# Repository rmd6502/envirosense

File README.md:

# envirosense
Crowdsourced Environmental Sensing

The pm (particulate measure) depends on Paul Van Haastrecht's
SPS30 library at https://github.com/paulvha/sps30. Sensirion's
library doesn't work, though I imagine they'll fix that.

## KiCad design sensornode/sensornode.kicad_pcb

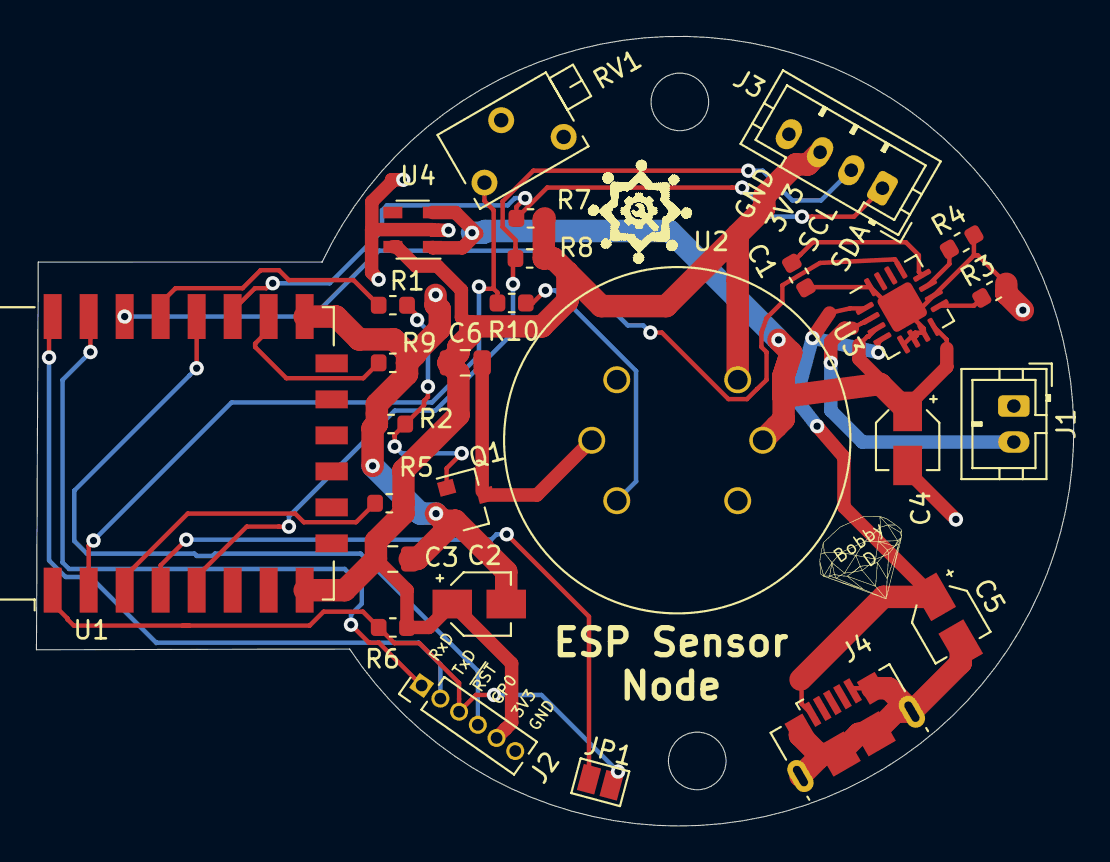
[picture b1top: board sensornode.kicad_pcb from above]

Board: 2 copper layers, 57.6 x 43.9 mm, 27 parts (0 on the bottom side), 23 nets.

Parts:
C1: 0.1u; C_0603_1608Metric
C2, C4: 10u; CP_Elec_3x5.3
C3: .1u; C_0805_2012Metric
C5: 1u; CP_Elec_3x5.3
C6: 10u ceramic; C_0805_2012Metric
J1: Conn_01x02; JST_PH_B2B-PH-K_1x02_P2.00mm_Vertical
J2: Conn_01x06_Male; PinHeader_1x06_P1.27mm_Vertical
J3: Conn_01x04_Male; JST_PH_B4B-PH-K_1x04_P2.00mm_Vertical
J4: USB_B_Micro; USB_Micro-B_GCT_USB3076-30-A
JP1: SolderJumper_2_Open; SolderJumper-2_P1.3mm_Open_Pad1.0x1.5mm
Q1: MMBT3904; SOT-23
R1: 1k; R_0603_1608Metric
R2, R5, R6, R9: 10k; R_0603_1608Metric
R3, R4: 97.6k; R_0603_1608Metric
R7, R8: 4.7k; R_0603_1608Metric
R10: 6k8; R_0603_1608Metric
RV1: 100k; Potentiometer_Bourns_3266X_Horizontal
U1: ESP-12F; ESP-12E
U2: MQ-135; MQ_13X
U3: LTC4055; QFN-16-1EP_4x4mm_P0.65mm_EP2.15x2.15mm
U4: MIC5504-3.3YM5; SOT-23-5

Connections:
+3V3: C2.1, C3.2, C6.1, J2.5, J3.3, R5.1, R6.1, R7.1, R8.1, U1.8, U2.1, U4.5
+5V: C4.1, U2.2, U3.3, U3.8, U4.1, U4.3
/GP0: J2.4, U1.18
/RX: J2.1, U1.21
/SCL: J3.2, R8.2, U1.5
/SDA: J3.1, R7.2, U1.17
/TX: J2.2, U1.22
/htron: R1.1, U1.19
/mq135_adc: R10.1, RV1.1, U1.2
/~RST: J2.3, JP1.2, R6.2, U1.1
/~acpr: U1.20, U3.13
GND: C1.2, C2.2, C3.1, C4.2, C5.2, J1.1, J2.6, J3.4, J4.5, J4.6, Q1.2, R2.1, R3.2, R4.2, R9.2, RV1.2, RV1.3, U1.15, U3.5, U3.6, U3.7, U3.10, U3.16, U3.17, U4.2
unnamed: C1.1, U3.12
unnamed: C6.2, Q1.3, U2.6
unnamed: J1.2, U3.2
unnamed: JP1.1, U1.4
unnamed: Q1.1, R1.2, R2.2
unnamed: R3.1, U3.9
unnamed: R4.1, U3.11
unnamed: R5.2, U1.3
unnamed: R9.1, U1.16
unnamed: R10.2, U2.5
VBUS: C5.1, J4.1, U3.1, U3.4

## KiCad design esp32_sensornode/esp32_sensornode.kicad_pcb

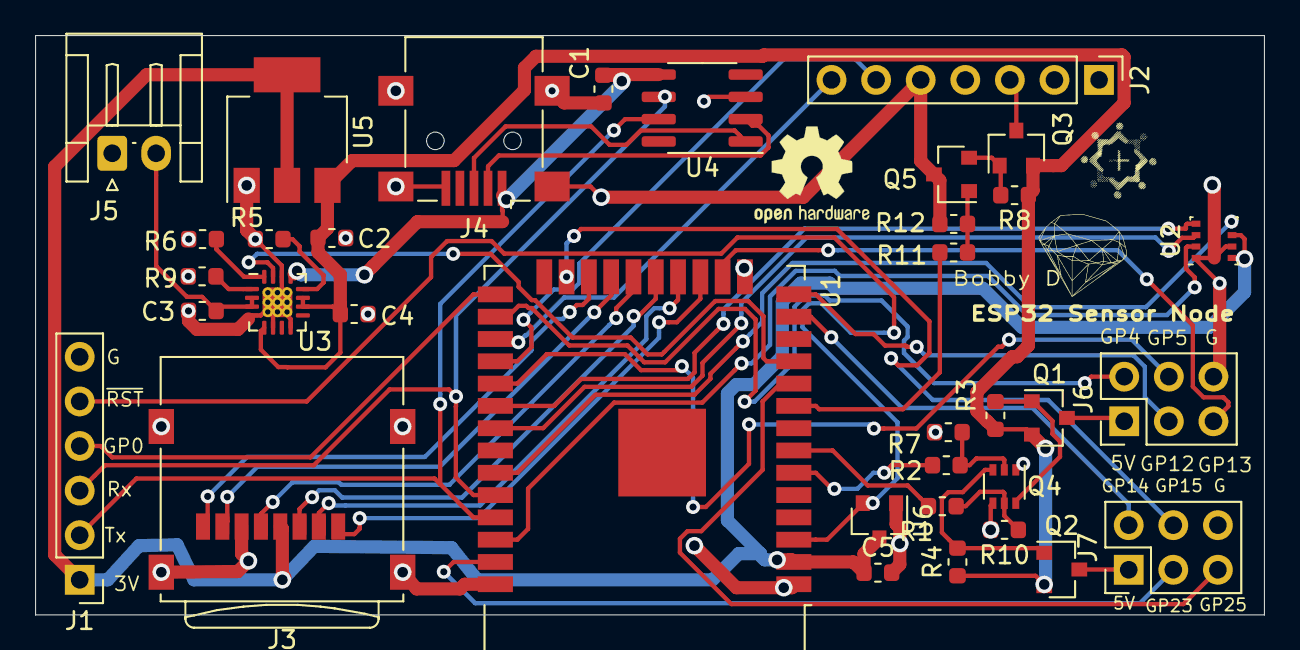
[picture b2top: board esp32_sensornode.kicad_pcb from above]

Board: 2 copper layers, 70.0 x 33.0 mm, 35 parts (0 on the bottom side), 47 nets.

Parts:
C1, C4: 2.2u 10v; C_0603_1608Metric
C2: 10u 10v; C_0603_1608Metric
C3: 2.2u 5v; C_0603_1608Metric
C5: 10u 5v; C_0603_1608Metric
J1: Conn_01x06_Female; PinHeader_1x06_P2.54mm_Vertical
J2: Conn_01x07_Male; PinHeader_1x07_P2.54mm_Vertical
J3: Micro_SD_Card; microSD_HC_Wuerth_693072010801
J4: USB_B_Mini; USB_Mini-B_Lumberg_2486_01_Horizontal
J5: Conn_01x02_Male; JST_EH_S2B-EH_1x02_P2.50mm_Horizontal
J6, J7: Conn_02x03_Odd_Even; PinHeader_2x03_P2.54mm_Vertical
Q1, Q2, Q3: NDS3332P; SOT-23
Q4: MMDT2222A; SOT-363_SC-70-6
Q5: MMBT2222A; SOT-23
R1, R2, R11: 220R; R_0603_1608Metric
R3, R4, R7, R8, R9, R10, R12: 10k; R_0603_1608Metric
R5: 1.18k; R_0603_1608Metric
R6: 1.13k; R_0603_1608Metric
U1: ESP32-WROOM-32
U2: BME280; Bosch_LGA-8_2.5x2.5mm_P0.65mm_ClockwisePinNumbering
U3: BQ24075; QFN-16-1EP_3x3mm_P0.5mm_EP1.7x1.7mm_ThermalVias
U4: CH330N; SOIC-8_3.9x4.9mm_P1.27mm
U5: LM1117-3.3; SOT-223-3_TabPin2
U6: TPS3839DBZ; SOT-23

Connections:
+3V3: C5.1, J1.1, J3.4, U1.2, U2.6, U2.8, U5.2, U6.3
+5V: C2.1, C4.1, Q1.2, Q2.2, Q3.2, R3.1, R4.1, R8.1, U3.5, U3.10, U3.11, U5.3
/BME280_MISO: U1.33, U2.5
/BME280_MOSI: U1.31, U2.3
/BME280_SCK: U1.30, U2.4
/CLK: J3.5, U1.20
/CMD: J3.3, U1.19
/D0: J3.7, U1.21
/D1: J3.8, U1.22
/D2: J3.1, U1.17
/D3: J3.2, U1.18
/EN: J1.5, U1.3, U6.2
/Enable_5V: U1.11, U3.15
/IO0: J1.4, U1.25
/IO4: J6.2, U1.26
/IO5: J6.4, U1.29
/IO12: J6.3, U1.14
/IO13: J6.5, U1.16
/IO14: J7.2, U1.13
/IO15: J7.4, U1.23
/IO23: J7.3, U1.37
/IO25: J7.5, U1.10
/RxD: J1.3, U1.34, U4.6
/SDS011_RxD: J2.6, U1.28
/SDS011_TxD: J2.7, U1.27
/TxD: J1.2, U1.35, U4.7
/USB_5V: C1.2, J4.1, U3.13, U4.5
/power_sao0: R2.2, U1.6
/power_sao1: R1.2, U1.7
/power_sds011: R11.2, U1.9
/~BME280_SS: U1.36, U2.2
GND: C1.1, C2.2, C3.2, C4.2, C5.2, J1.6, J2.5, J3.6, J3.9, J4.5, J4.6, J5.1, J6.6, J7.6, Q4.1, Q4.4, Q5.3, R5.2, R6.2, R7.2, R9.2, R10.2, R12.2, U1.1, U1.15, U1.38, U2.1, U2.7, U3.4, U3.6, U3.8, U3.14, U3.17, U4.3, U5.1, U6.1
unnamed: C3.1, J5.2, U3.2, U3.3
unnamed: J2.3, Q3.3
unnamed: J4.2, U4.2
unnamed: J4.3, U4.1
unnamed: J6.1, Q1.3
unnamed: J7.1, Q2.3
unnamed: Q1.1, Q4.6, R3.2
unnamed: Q2.1, Q4.3, R4.2
unnamed: Q3.1, Q5.2, R8.2
unnamed: Q4.2, R2.1, R7.1
unnamed: Q4.5, R1.1, R10.1
unnamed: Q5.1, R11.1, R12.1
unnamed: R5.1, U3.12
unnamed: R6.1, U3.16
unnamed: R9.1, U3.1

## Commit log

2019-05-06 add sensornode
2019-05-16 update to latest
2019-05-22 update board
2019-05-22 add c6, relayout
2019-05-22 make vbus .75mm
2019-05-23 update layout
2019-05-23 update schematic
2019-05-23 fix text items for clarity
2019-05-28 tweaks, add jumper for programming
2019-05-28 add diamond logo
2019-05-28 add missing libs and footprints, add jumper for programming
2019-05-28 add gerbers
2019-05-28 add back mounting holes?
2019-05-28 fix holes, export png and step
2019-05-29 try to get a 3d render that is manifold
2019-06-02 remove duplicate items which caused non-manifold model
2019-06-14 add acpower indication
2019-06-21 add firmware v0
2019-06-22 remove comment, add printf
2019-06-23 use stl to simplify average
2019-06-23 add mq135 library
2019-08-28 cleanup git repo
2019-08-28 remove submodules
2019-09-16 use http instead of mqtt
2019-09-16 send content type and capture time
2019-12-25 split pm
2019-12-26 add sensing, update readme
2019-12-27 get it sending, fix wifimanager, 30 min sleep
2020-01-02 add esp32 node
2020-01-02 add arch image
2020-04-01 firmware
2020-04-01 esp32
